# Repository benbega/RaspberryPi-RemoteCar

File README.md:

# RaspberryPi-RemoteCar
Repository hosting code for my RC car project based on the Raspberry Pi 4B+

## **Introduction**

This is a remote controlled car based on two Raspberry Pi 4B+ single board computers. The car chassis is from an old kit for collegiate competitions that I got for free from my university electronics stockroom. The car is powered by 2 7V DC motors, capable of approximately 23,000 RPM without a load.

A more robust document with project details will be posted as a PDF in this repository soon, containing a list of the exact hardware being used and instructions to setup the project yourself.

[A video of the project's current state can be found by clicking here](https://youtu.be/IsMrb5jVGqQ) 

## **Car Setup**

The car portion of the project contains a chassis, two DC motors, a servo, a Raspberry Pi 4B+, and a custom PCB. The PCB was fully custom designed, and incorporates an L293D motor driver chip, as well as indicator LEDs, signal pins for the servo, and hookups for the system's battery. The car uses a small 7V battery to power all of the microelectronic components, as well as a 5V 3A battery pack to power the Raspberry Pi. Although the dual battery system is extremely heavy and inefficient, it was chosen to suit the Raspberry Pi's high current demands.

The design files and information about the custom PCB can be found in the RaspiCar_PCB2 folder in this GitHub repository.

## **Wireless Communication**

The wireless controller functionality is implemented by utilizing the Raspberry Pi's remote GPIO functionality through the gpiozero library. The Raspberry Pi powering the controller is setup to be a wireless access point, which the car's Raspberry Pi connects to automatically upon boot. This allows the Remote GPIO setup to work anywhere, not just in specific locations that have a prexisting WiFi network. While lower power Raspberry Pi models, or microcointrollers could likely be used to accomplish the same functionality, these are the boards I currently have, and there is no reason currently to change the design.

## **State of the Project**

The project is currently in a complete state, where all systems are functional as originally designed. The car is able to freely drive and steer, and starts in a driveable state upon boot. The car is heavier than originally designed due to the Raspberry Pi power supply, so the top speed is relatively low.

## **Looking Forward**

I do not currently have plans to update this project, as I am focusing on something else I will write about soon, but in the future my goal is to switch out the motors and servo for significantly more powerful options, and utilize a more efficient LiPo battery pack. A related near term project I plan on completing is a short, detailed write up on how the Raspberry Pi Remote GPIO is setup, as I think it is one of the more interesting aspects of the overall design.

--

This project is licensed under the terms of the MIT license

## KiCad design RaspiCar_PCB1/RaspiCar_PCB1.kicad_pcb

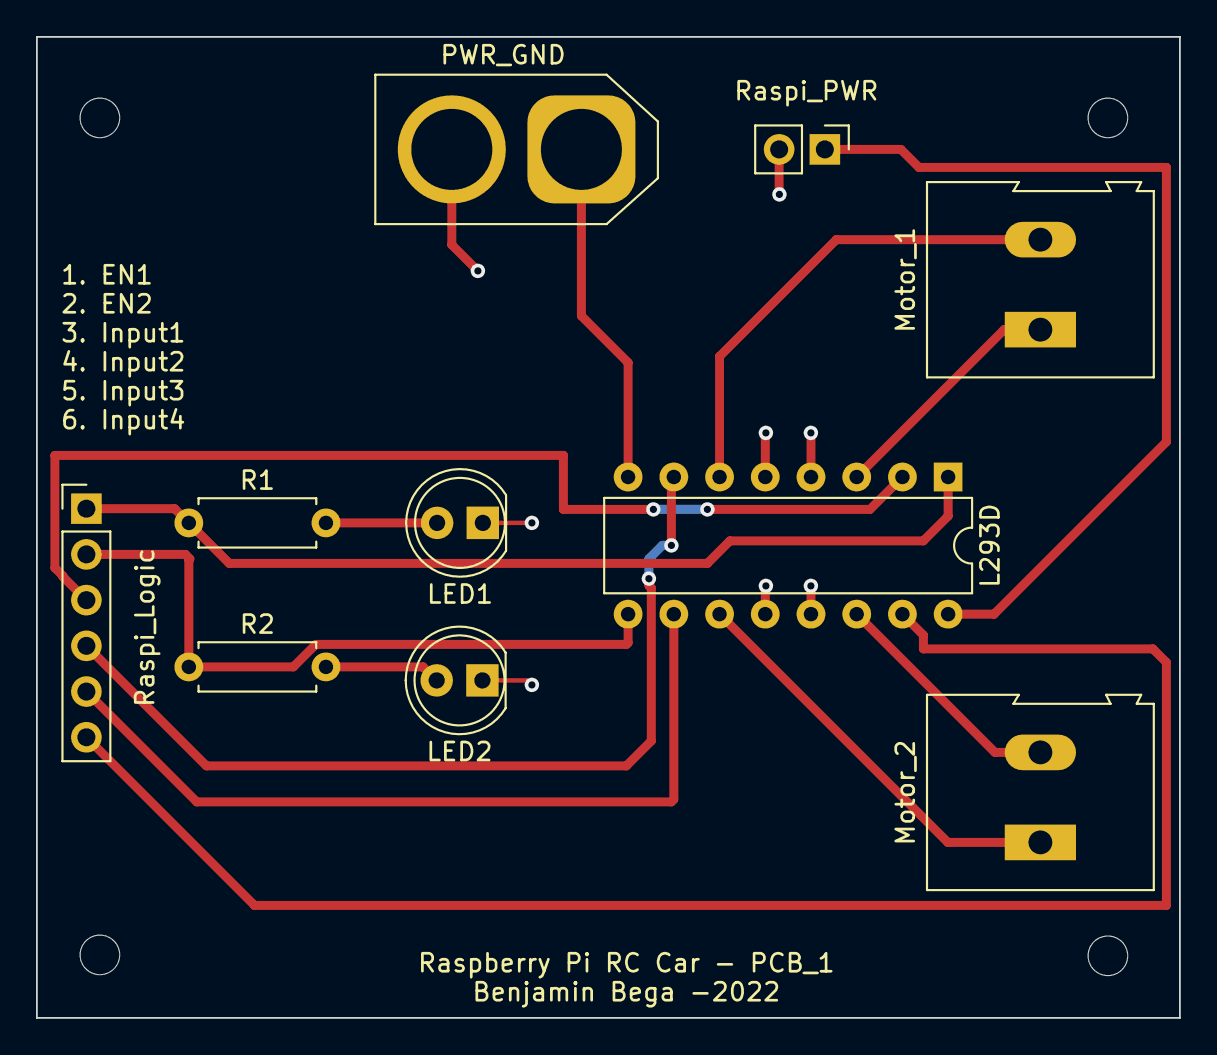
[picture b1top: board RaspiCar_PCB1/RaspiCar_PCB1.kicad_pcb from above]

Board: 2 copper layers, 63.5 x 54.5 mm, 14 parts (0 on the bottom side), 15 nets.

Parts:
H1, H2, H3, H4: MountingHole; MountingHole_2.2mm_M2
L293D: L293D; DIP-16_W7.62mm
LED1: LED1; LED_D5.0mm
LED2: LED2; LED_D5.0mm
Motor_1: MotorTerminal1; TerminalBlock_Altech_AK300-2_P5.00mm
Motor_2: MotorTerminal2; TerminalBlock_Altech_AK300-2_P5.00mm
PWR_GND: PWR_GND; AMASS_XT60-F_1x02_P7.20mm_Vertical
R1, R2: 3.3k; R_Axial_DIN0207_L6.3mm_D2.5mm_P7.62mm_Horizontal
Raspi_Logic: PiLogicHeaders; PinHeader_1x06_P2.54mm_Vertical
Raspi_PWR: RaspiPWR/GND; PinHeader_1x02_P2.54mm_Vertical

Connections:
+5V: L293D.16 (VCC1), Raspi_PWR.1
+7.5V: L293D.8 (VCC2), PWR_GND.1
GND: L293D.4 (GND), L293D.5 (GND), L293D.12 (GND), L293D.13 (GND), LED1.1 (K), LED2.1 (K), PWR_GND.2, Raspi_PWR.2
unnamed: L293D.1 (EN1,2), R1.1, Raspi_Logic.1
unnamed: L293D.2 (1A), Raspi_Logic.3
unnamed: L293D.3 (1Y), Motor_1.1
unnamed: L293D.6 (2Y), Motor_1.2
unnamed: L293D.7 (2A), Raspi_Logic.4
unnamed: L293D.9 (EN3,4), R2.1, Raspi_Logic.2
unnamed: L293D.10 (3A), Raspi_Logic.5
unnamed: L293D.11 (3Y), Motor_2.1
unnamed: L293D.14 (4Y), Motor_2.2
unnamed: L293D.15 (4A), Raspi_Logic.6
unnamed: LED1.2 (A), R1.2
unnamed: LED2.2 (A), R2.2

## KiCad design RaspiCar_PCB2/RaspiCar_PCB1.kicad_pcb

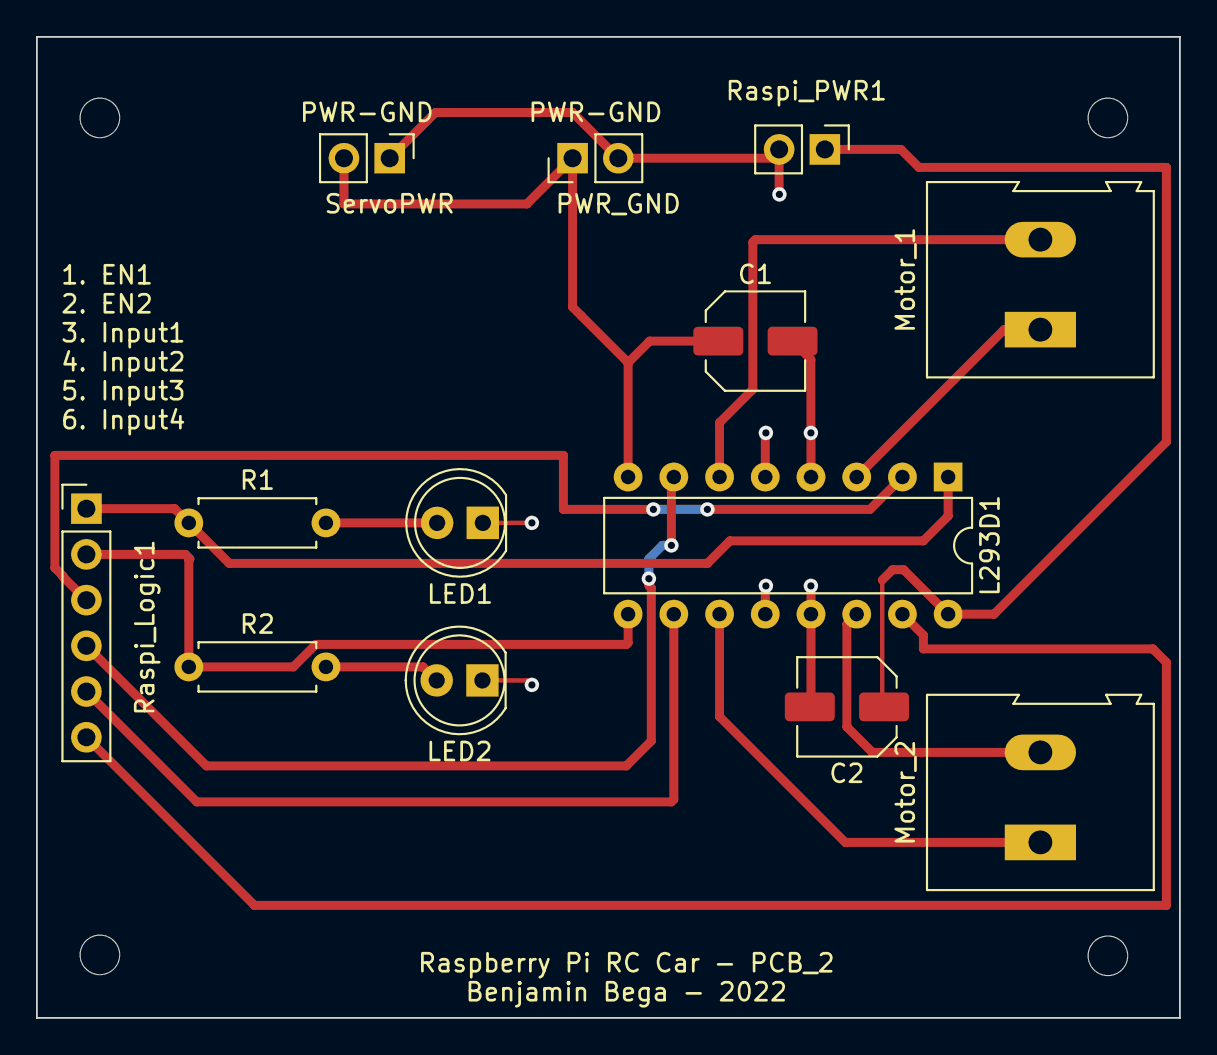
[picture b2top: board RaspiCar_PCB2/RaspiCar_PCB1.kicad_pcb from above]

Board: 2 copper layers, 63.5 x 54.5 mm, 17 parts (0 on the bottom side), 15 nets.

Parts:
C1, C2: 1uF; C_Elec_5x5.4
H1, H2, H3, H4: MountingHole; MountingHole_2.2mm_M2
L293D1: L293D; DIP-16_W7.62mm
LED1: LED1; LED_D5.0mm
LED2: LED2; LED_D5.0mm
Motor_1: MotorTerminal1; TerminalBlock_Altech_AK300-2_P5.00mm
Motor_2: MotorTerminal2; TerminalBlock_Altech_AK300-2_P5.00mm
PWR_GND: PWR_GND; PinHeader_1x02_P2.54mm_Vertical
R1, R2: 3.3k; R_Axial_DIN0207_L6.3mm_D2.5mm_P7.62mm_Horizontal
Raspi_Logic1: PiLogicHeaders; PinHeader_1x06_P2.54mm_Vertical
Raspi_PWR1: RaspiPWR/GND; PinHeader_1x02_P2.54mm_Vertical
ServoPWR: ServoPWR/GND; PinHeader_1x02_P2.54mm_Vertical

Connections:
+5V: C2.1, L293D1.16 (VCC1), Raspi_PWR1.1
+7.5V: C1.1, L293D1.8 (VCC2), PWR_GND.1, ServoPWR.2
GND: C1.2, C2.2, L293D1.4 (GND), L293D1.5 (GND), L293D1.12 (GND), L293D1.13 (GND), LED1.1 (K), LED2.1 (K), PWR_GND.2, Raspi_PWR1.2, ServoPWR.1
unnamed: L293D1.1 (EN1,2), R1.1, Raspi_Logic1.1
unnamed: L293D1.2 (1A), Raspi_Logic1.3
unnamed: L293D1.3 (1Y), Motor_1.1
unnamed: L293D1.6 (2Y), Motor_1.2
unnamed: L293D1.7 (2A), Raspi_Logic1.4
unnamed: L293D1.9 (EN3,4), R2.1, Raspi_Logic1.2
unnamed: L293D1.10 (3A), Raspi_Logic1.5
unnamed: L293D1.11 (3Y), Motor_2.1
unnamed: L293D1.14 (4Y), Motor_2.2
unnamed: L293D1.15 (4A), Raspi_Logic1.6
unnamed: LED1.2 (A), R1.2
unnamed: LED2.2 (A), R2.2

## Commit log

2022-04-02 README v0.01
    Updated README with initial project details
2022-04-02 Added Licensing
2022-04-02 Added MotorController Test Script
2022-10-03 CarPCB Commit
    Includes files for the PCB, version 1
2022-11-22 RaspiCar_0.2
    Added second PCB revision and full controller code
2023-03-03 Edited ReadME to indicate project completion
2023-03-03 Fixed folder names and ReadMe
